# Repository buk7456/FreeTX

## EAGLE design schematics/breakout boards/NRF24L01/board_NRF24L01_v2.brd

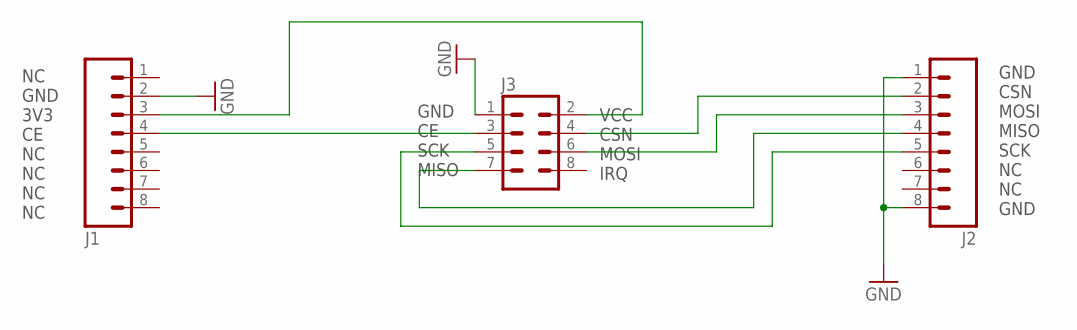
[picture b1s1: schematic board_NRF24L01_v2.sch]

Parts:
J1, J2: M08; 1X08_ROUND
J3: M04X2; 2X4

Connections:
GND: J1.2, J2.1, J2.8, J3.1
unnamed: J1.3, J3.2
unnamed: J2.5, J3.5
unnamed: J2.4, J3.7
unnamed: J2.3, J3.6
unnamed: J1.4, J3.3
unnamed: J2.2, J3.4

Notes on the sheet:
VCC CSN MOSI IRQ
GND CE SCK MISO
GND CSN MOSI MISO SCK NC NC GND
NC GND 3V3 CE NC NC NC NC

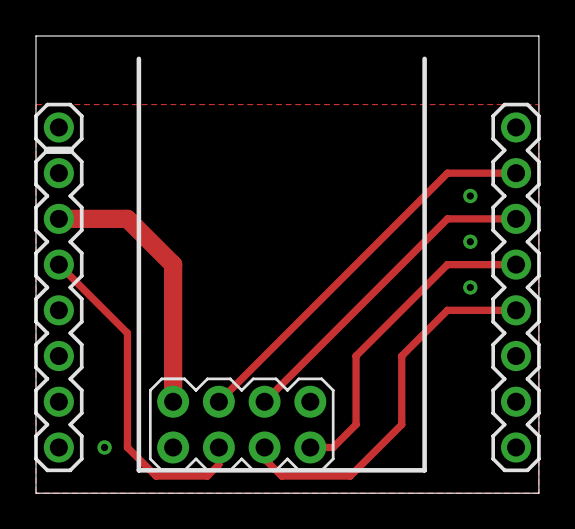
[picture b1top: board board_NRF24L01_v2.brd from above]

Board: 2 copper layers, 27.9 x 25.4 mm, 3 parts (0 on the bottom side), 7 nets.

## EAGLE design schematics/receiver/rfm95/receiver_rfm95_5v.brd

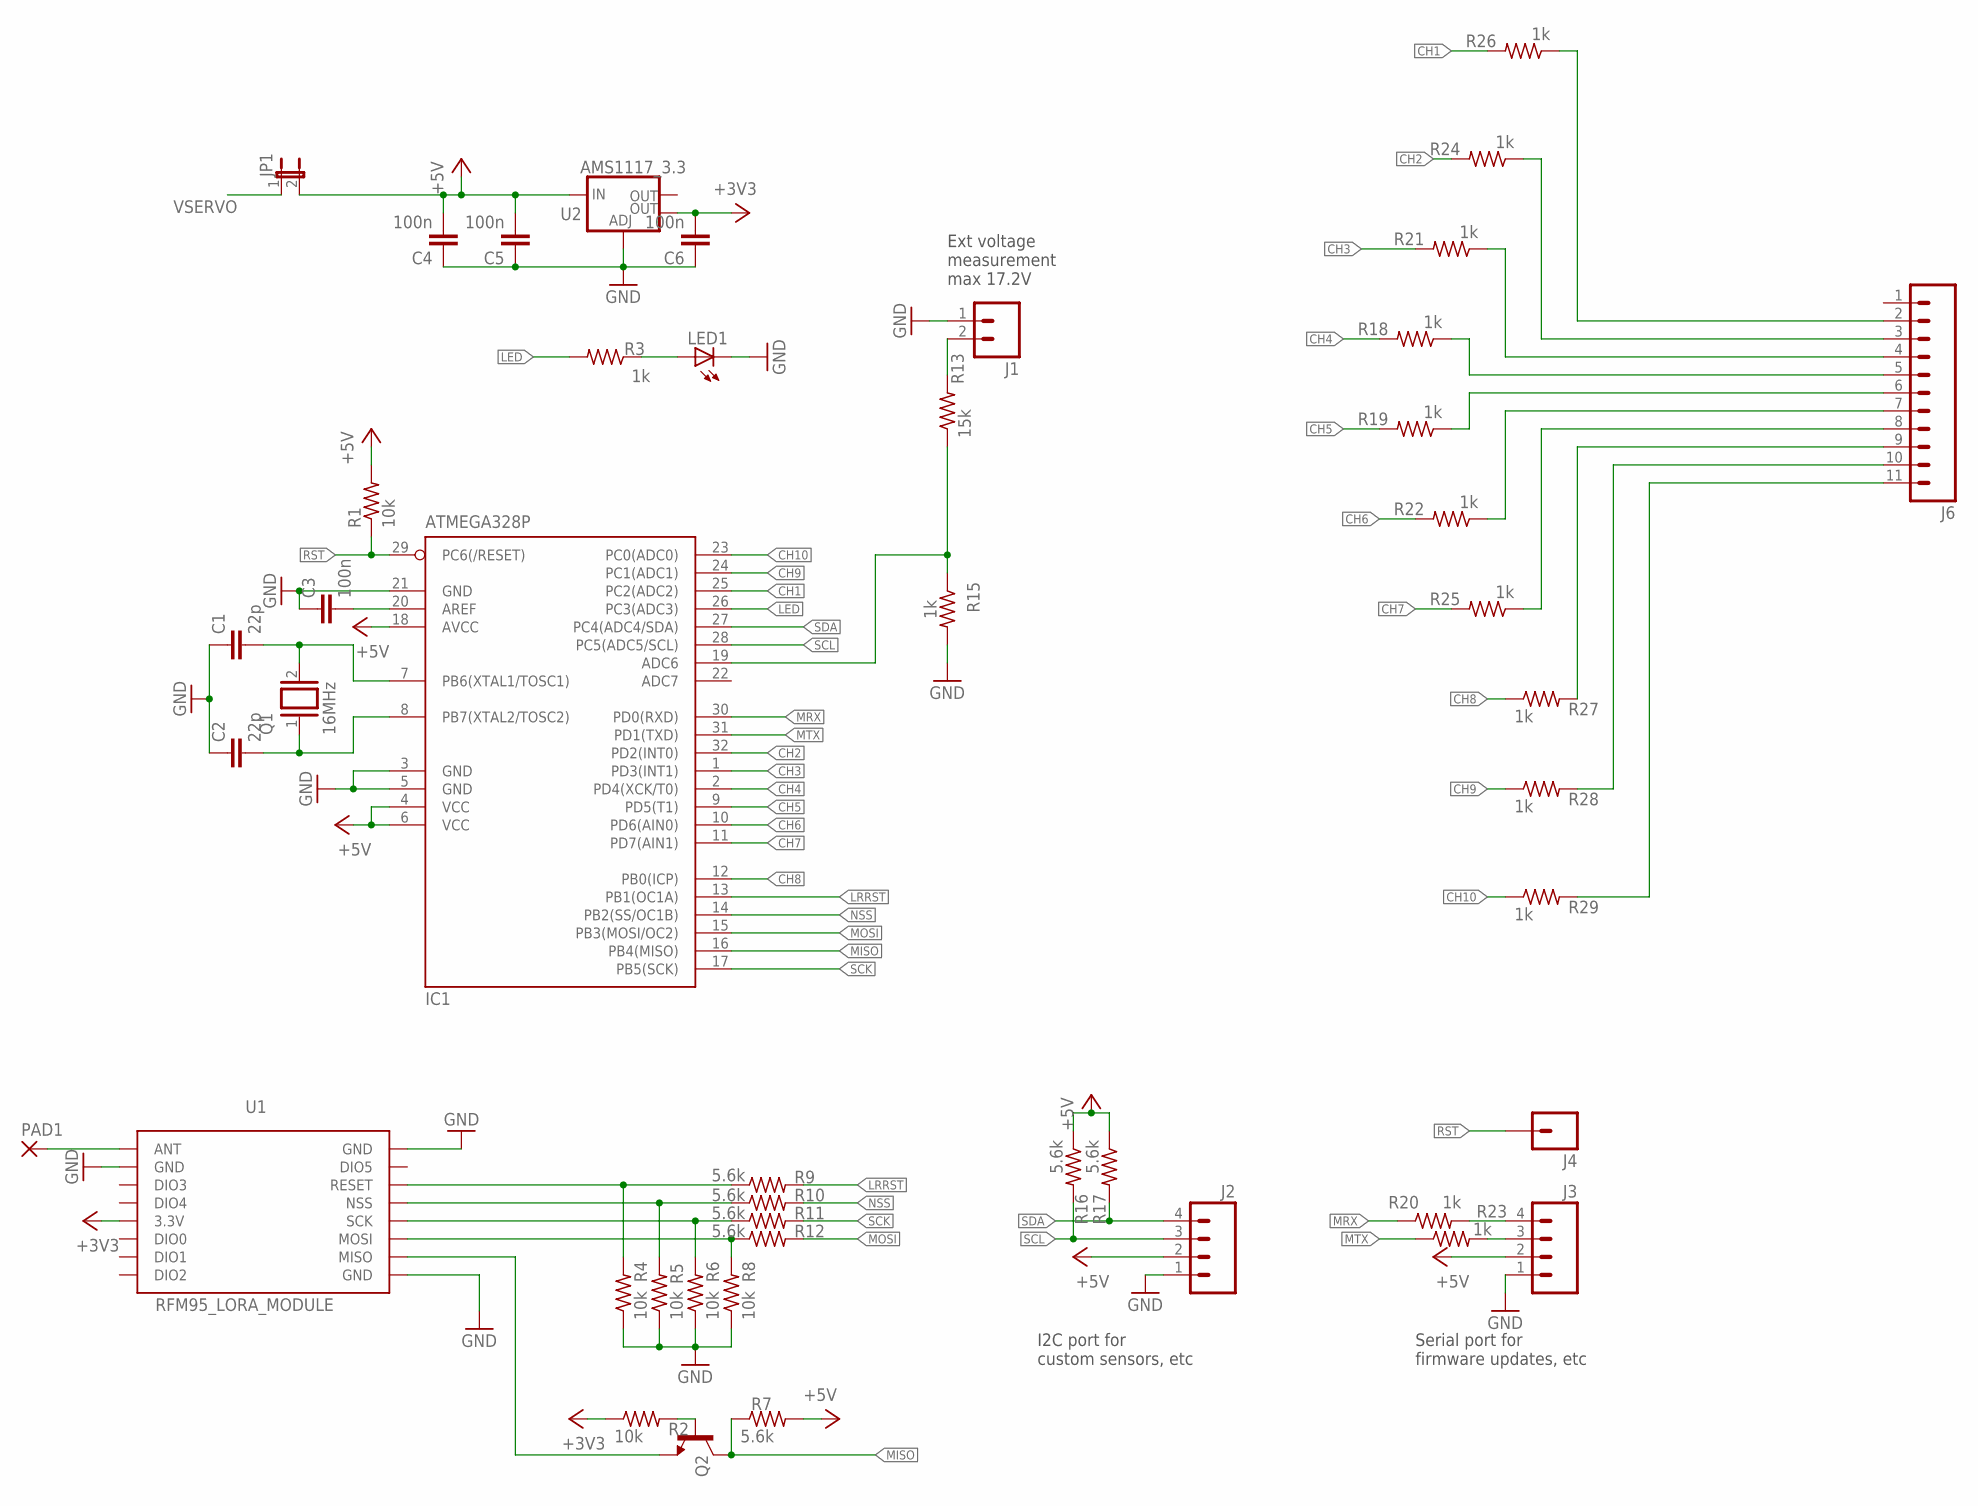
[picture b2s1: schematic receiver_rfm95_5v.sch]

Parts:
C1, C2: 22p; C0805K
C3, C4, C5, C6: 100n; C0805K
IC1: ATMEGA328P; TQFP32-08
J1: M02PTH; 1X02
J2, J3: M04PTH; 1X04
J4: M01PTH; 1X01
J6: M11PTH; 1X11
JP1: JP1E; JP1
LED1: LEDCHIPLED_1206; CHIPLED_1206
PAD1: 2,15/1,0
Q1: 16MHz; QS
Q2: BC817-16SMD; SOT23-BEC
R1, R2, R4, R5, R6, R8: 10k; R0805
R3, R15, R18, R19, R20, R21, R22, R23, R24, R25, R26, R27, R28, R29: 1k; R0805
R7, R9, R10, R11, R12, R16, R17: 5.6k; R0805
R13: 15k; R0805
U1: RFM95_LORA_MODULE; RFM95
U2: AMS1117_3.3; SOT223

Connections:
+3V3: C6.2, R2.1, U1.3.3V, U2.4 (OUT)
+5V: C4.2, C5.2, IC1.4 (VCC), IC1.6 (VCC), IC1.18 (AVCC), J2.2, J3.2, JP1.2, R1.2, R7.2, R16.1, R17.1, U2.3 (IN)
CH1: IC1.25 (PC2(ADC2)), R26.2
CH2: IC1.32 (PD2(INT0)), R24.2
CH3: IC1.1 (PD3(INT1)), R21.2
CH4: IC1.2 (PD4(XCK/T0)), R18.2
CH5: IC1.9 (PD5(T1)), R19.2
CH6: IC1.10 (PD6(AIN0)), R22.2
CH7: IC1.11 (PD7(AIN1)), R25.2
CH8: IC1.12 (PB0(ICP)), R27.1
CH9: IC1.24 (PC1(ADC1)), R28.1
CH10: IC1.23 (PC0(ADC0)), R29.1
DIO3: U1.DIO3
GND: C1.1, C2.1, C3.1, C4.1, C5.1, C6.1, IC1.3 (GND), IC1.5 (GND), IC1.21 (GND), J1.1, J2.1, J3.1, LED1.C, R4.1, R5.1, R6.1, R8.1, R15.2, U1.GND, U1.GND@1 (GND), U1.GND@2 (GND), U2.1 (ADJ)
LED: IC1.26 (PC3(ADC3)), R3.2
LRRST: IC1.13 (PB1(OC1A)), R9.2
MISO: IC1.16 (PB4(MISO)), Q2.C, R7.1
MOSI: IC1.15 (PB3(MOSI/OC2)), R12.2
MRX: IC1.30 (PD0(RXD)), R20.1
MTX: IC1.31 (PD1(TXD)), R23.1
unnamed: C1.2, IC1.7 (PB6(XTAL1/TOSC1)), Q1.2
unnamed: J6.10, R28.2
unnamed: C2.2, IC1.8 (PB7(XTAL2/TOSC2)), Q1.1
unnamed: J6.9, R27.2
unnamed: R4.2, R9.1, U1.RESET
unnamed: R5.2, R10.1, U1.NSS
unnamed: R6.2, R11.1, U1.SCK
unnamed: R8.2, R12.1, U1.MOSI
unnamed: Q2.E, U1.MISO
unnamed: C3.2, IC1.20 (AREF)
unnamed: IC1.19 (ADC6), R13.1, R15.1
unnamed: J3.3, R23.2
unnamed: LED1.A, R3.1
unnamed: PAD1.1, U1.ANT
unnamed: J6.2, R26.1
unnamed: J3.4, R20.2
unnamed: J6.3, R24.1
unnamed: J6.4, R21.1
unnamed: J6.5, R18.1
unnamed: J6.6, R19.1
unnamed: J6.7, R22.1
unnamed: J6.8, R25.1
unnamed: Q2.B, R2.2
unnamed: J1.2, R13.2
unnamed: J6.11, R29.2
NSS: IC1.14 (PB2(SS/OC1B)), R10.2
RST: IC1.29 (PC6(/RESET)), J4.1, R1.1
SCK: IC1.17 (PB5(SCK)), R11.2
SCL: IC1.28 (PC5(ADC5/SCL)), J2.3, R16.2
SDA: IC1.27 (PC4(ADC4/SDA)), J2.4, R17.2
VSERVO: JP1.1

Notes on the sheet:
I2C port for custom sensors, etc
Serial port for firmware updates, etc
Ext voltage measurement max 17.2V

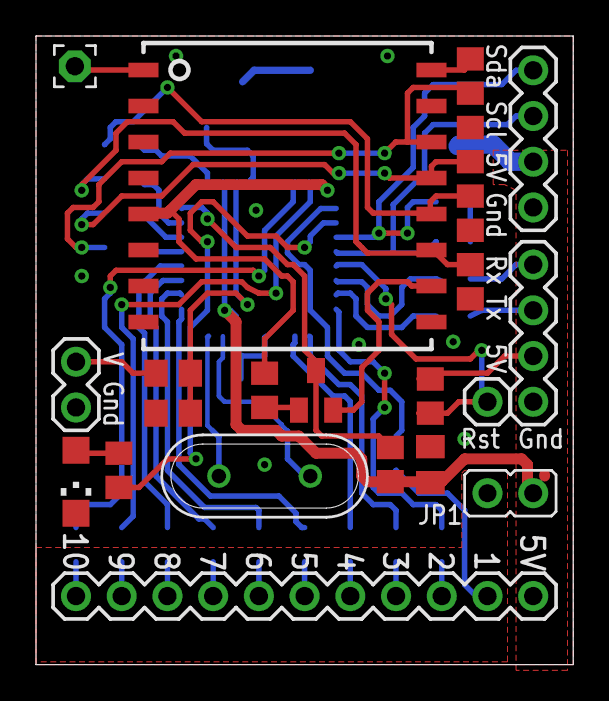
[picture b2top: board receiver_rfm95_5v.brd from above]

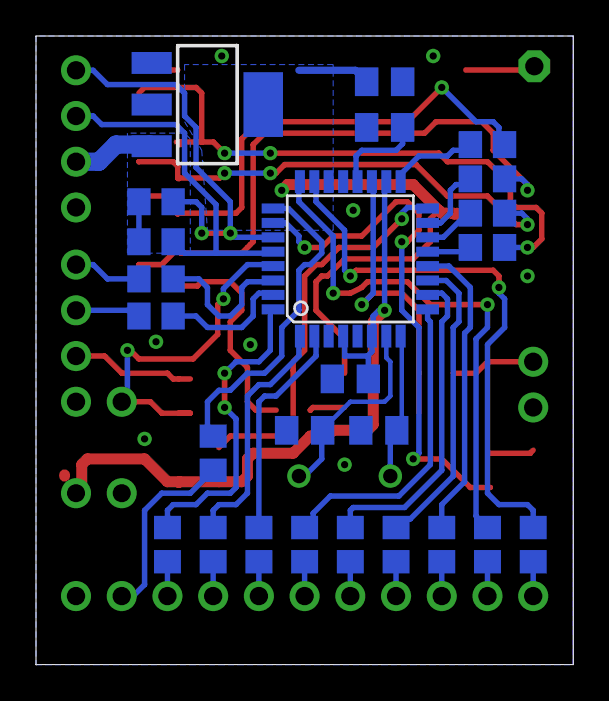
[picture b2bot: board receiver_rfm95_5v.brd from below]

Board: 2 copper layers, 29.8 x 34.9 mm, 47 parts (25 on the bottom side), 49 nets.

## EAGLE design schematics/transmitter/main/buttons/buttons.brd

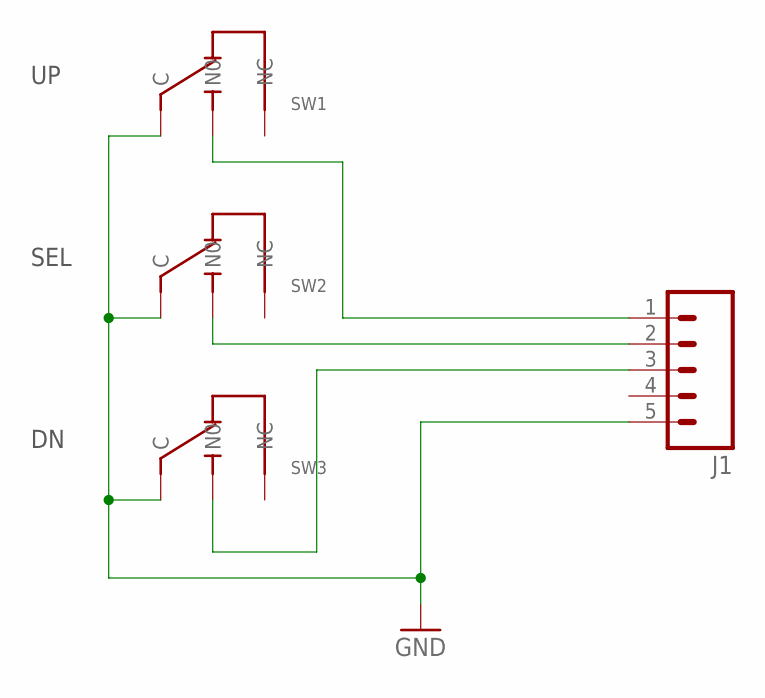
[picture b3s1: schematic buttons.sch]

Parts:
J1: M05PTH; 1X05
SW1, SW2, SW3: MICROSWITCH

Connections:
GND: J1.5, SW1.C, SW2.C, SW3.C
unnamed: J1.1, SW1.NO (N0)
unnamed: J1.3, SW3.NO (N0)
unnamed: J1.2, SW2.NO (N0)

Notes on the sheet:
SEL

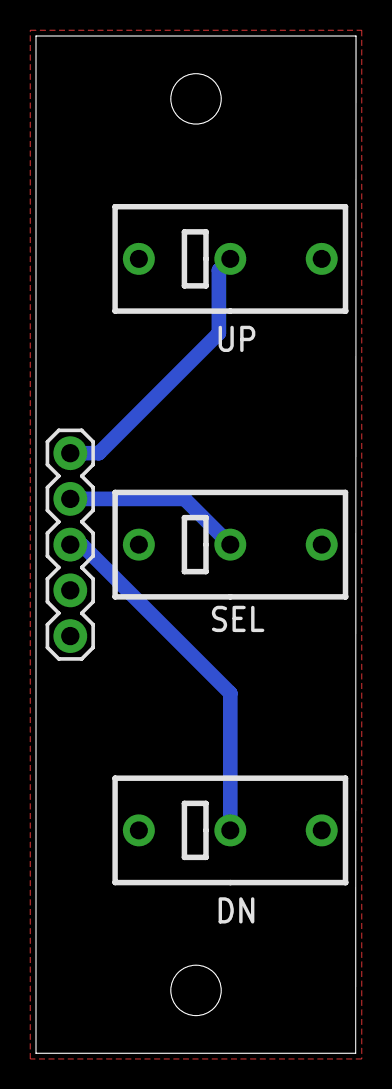
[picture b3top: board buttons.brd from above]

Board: 2 copper layers, 17.8 x 56.5 mm, 4 parts (0 on the bottom side), 4 nets.

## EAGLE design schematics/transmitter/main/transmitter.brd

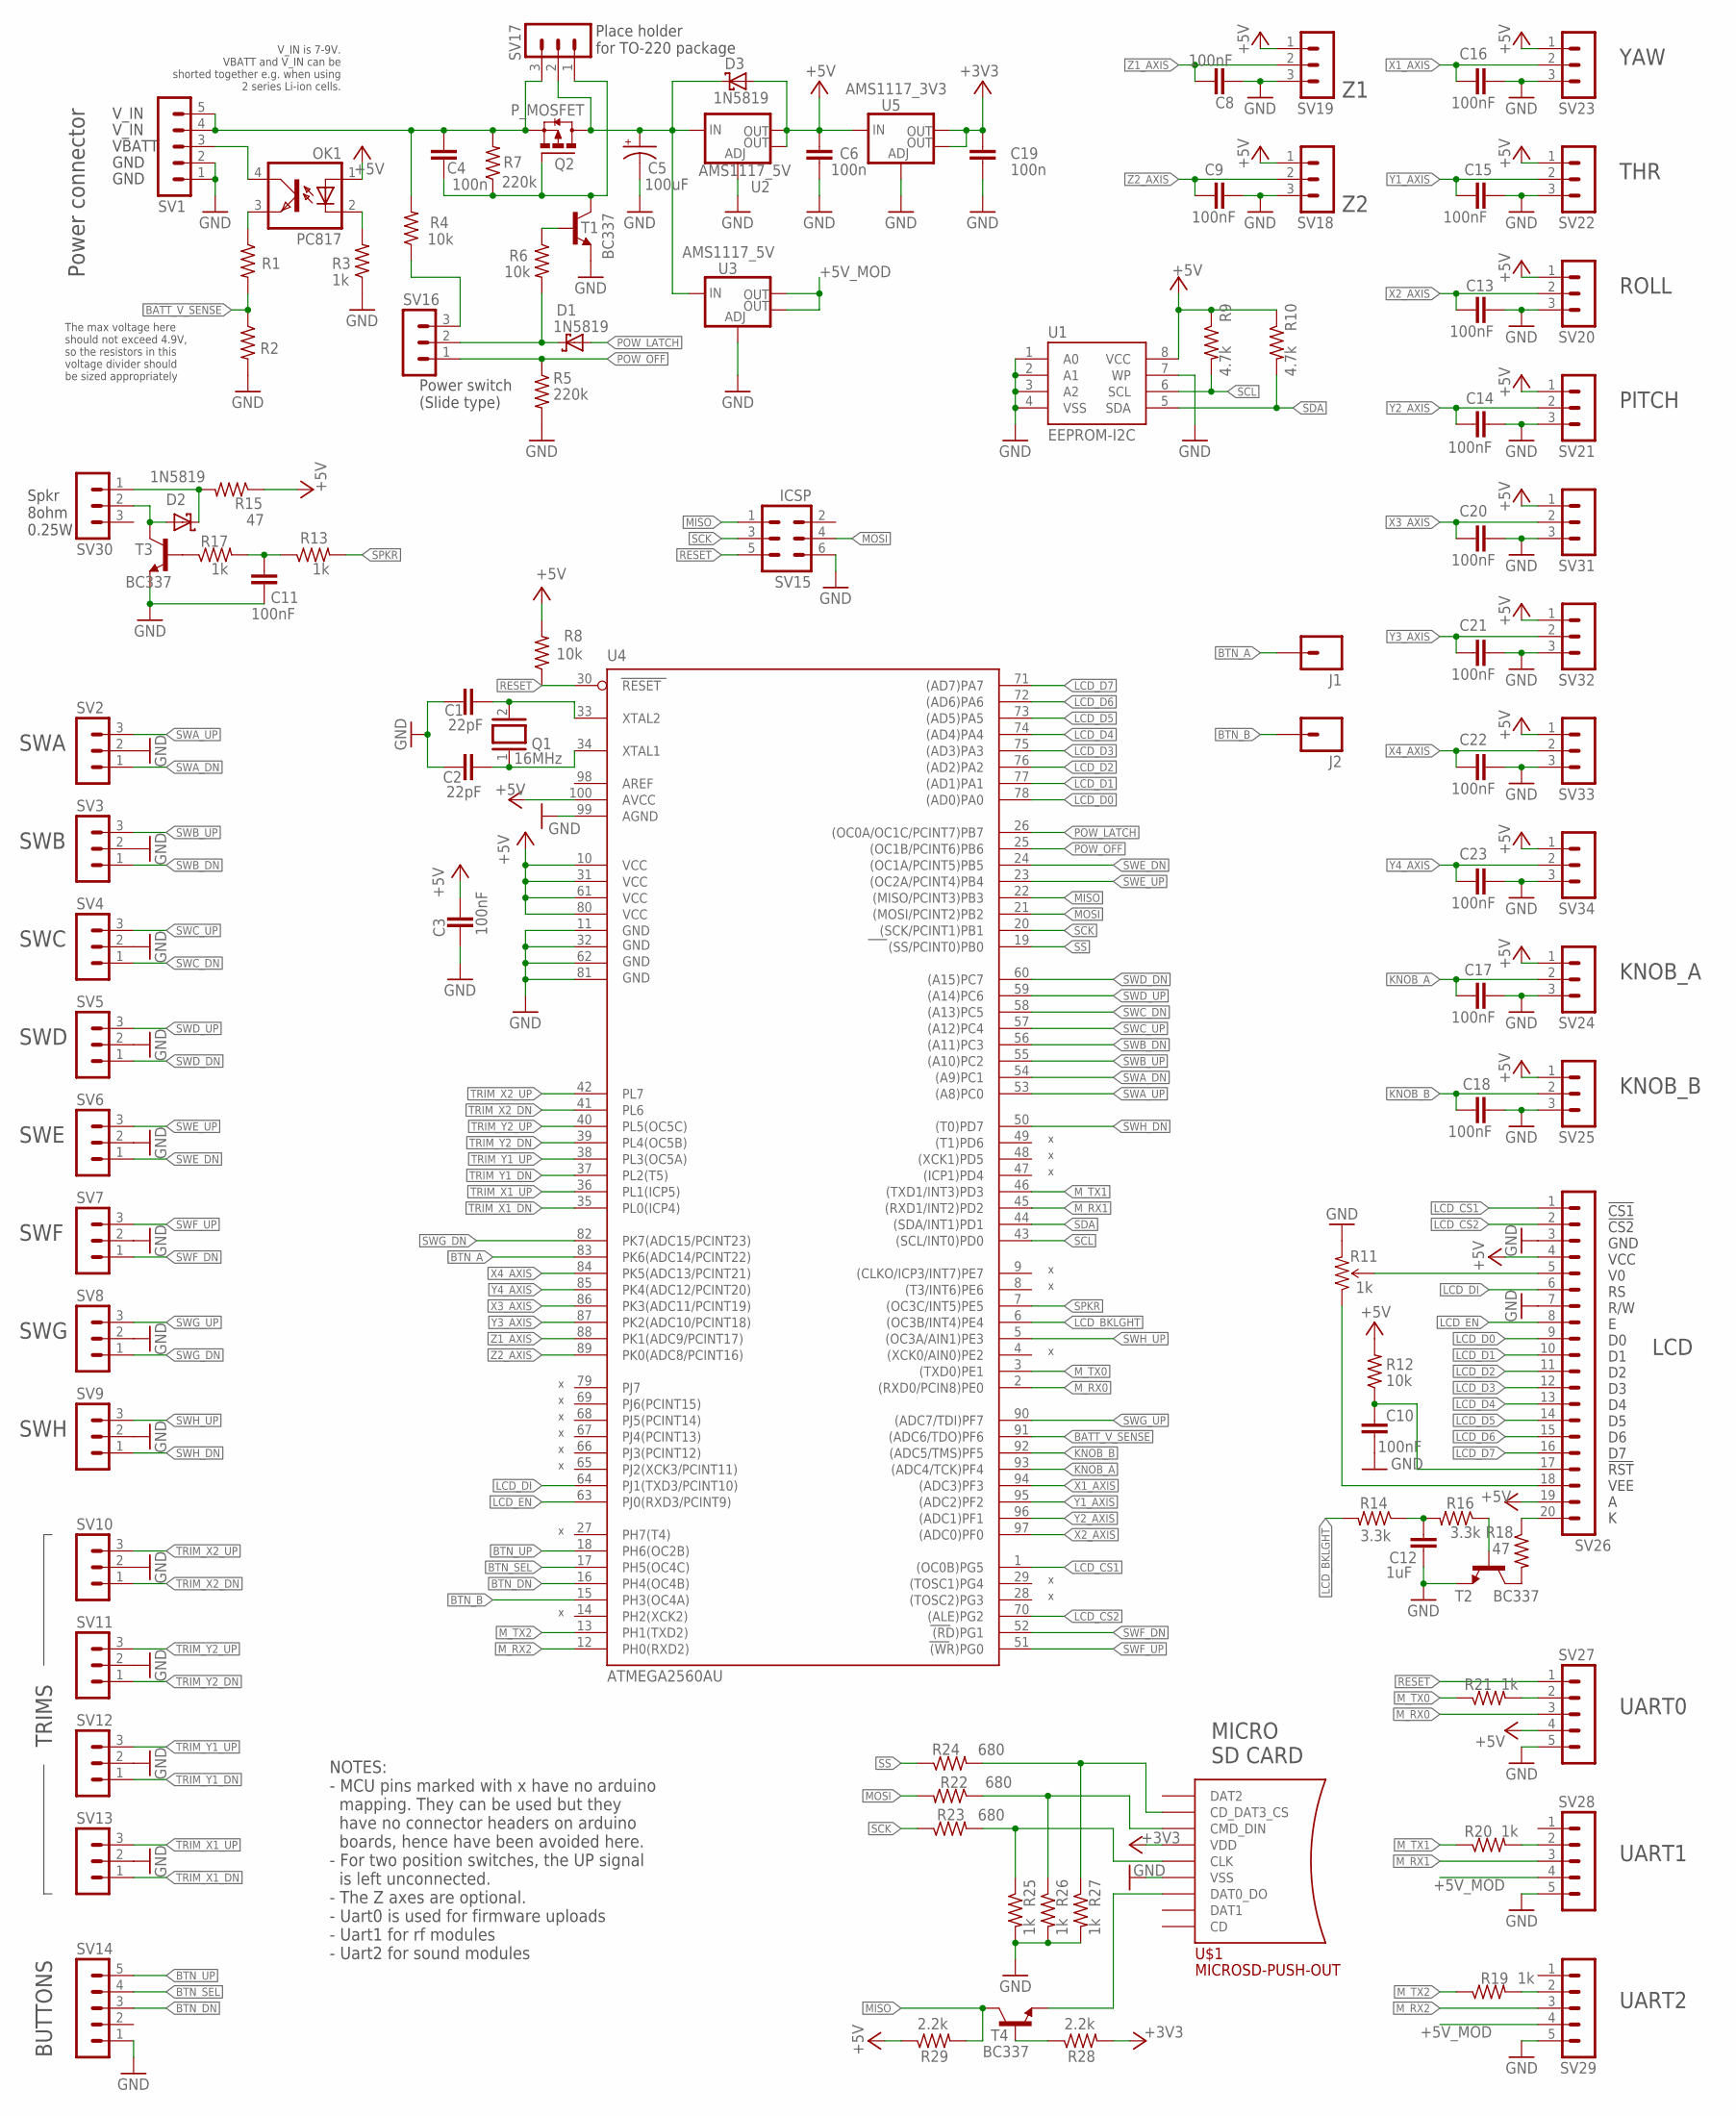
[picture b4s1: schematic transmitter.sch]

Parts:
C1, C2: 22pF; C050-024X044
C3, C8, C9, C10, C11, C13, C14, C15, C16, C17, C18, C20, C21, C22, C23: 100nF; C050-024X044
C4, C6, C19: 100n; C050-024X044
C5: 100uF; E2,5-6E
C12: 1uF; C050-024X044
D1, D2, D3: 1N5819; DO41-7.6
J1, J2: M01PTH_LONGPAD; 1X01_LONGPAD
OK1: PC817; DIL04
Q1: 16MHz; QS
Q2: P_MOSFET; SUPER-SOT3
R1, R2, R3, R13, R17, R19, R20, R21, R25, R26, R27: 1k; 0204/5
R4, R6, R8, R12: 10k; 0204/5
R5, R7: 220k; 0204/5
R9, R10: 4.7k; 0204/5
R11: 1k; TRIM_POT_PTH
R14, R16: 3.3k; 0204/5
R15, R18: 47; 0204/5
R22, R23, R24: 680; 0204/5
R28, R29: 2.2k; 0204/5
SV1, SV14, SV27, SV28, SV29: MA05-1
SV2, SV3, SV4, SV5, SV6, SV7, SV8, SV9, SV10, SV11, SV12, SV13, SV16, SV17, SV18, SV19, SV20, SV21, SV22, SV23, SV24, SV25, SV30, SV31, SV32, SV33, SV34: MA03-1
SV15: ICSP; MA03-2
SV26: MA20-1
T1, T2, T3, T4: BC337; TO92
U1: EEPROM-I2C; SO08-EIAJ
U2, U3: AMS1117_5V; SOT223
U4: ATMEGA2560AU; TQFP100
U5: AMS1117_3V3; SOT223
U$1: MICROSD-PUSH-OUT

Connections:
+3V3: C19.2, R28.2, U5.2 (OUT), U5.4 (OUT), U$1.4 (VDD)
+5V: C3.1, C6.2, D3.A, OK1.1 (A), R8.2, R9.1, R10.1, R12.2, R15.1, R29.1, SV18.1, SV19.1, SV20.1, SV21.1, SV22.1, SV23.1, SV24.1, SV25.1, SV26.4, SV26.19, SV27.4, SV31.1, SV32.1, SV33.1, SV34.1, U1.8 (VCC), U2.2 (OUT), U2.4 (OUT), U4.10 (VCC), U4.31 (VCC1), U4.61 (VCC2), U4.80 (VCC3), U4.100 (AVCC), U5.3 (IN)
+5V_MOD: SV28.4, SV29.4, U3.2 (OUT), U3.4 (OUT)
BATT_V_SENSE: R1.2, R2.1, U4.91 ((ADC6/TDO)PF6)
BTN_A: J1.1, U4.83 (PK6(ADC14/PCINT22))
BTN_B: J2.1, U4.15 (PH3(OC4A))
BTN_DN: SV14.3, U4.16 (PH4(OC4B))
BTN_SEL: SV14.4, U4.17 (PH5(OC4C))
BTN_UP: SV14.5, U4.18 (PH6(OC2B))
GND: C1.1, C2.1, C3.2, C5.-, C6.1, C8.2, C9.1, C10.2, C11.2, C12.2, C13.1, C14.1, C15.1, C16.1, C17.1, C18.1, C19.1, C20.1, C21.1, C22.1, C23.1, R2.2, R3.1, R5.2, R11.3 (CW), R25.2, R26.2, R27.2, SV1.1, SV1.2, SV2.2, SV3.2, SV4.2, SV5.2, SV6.2, SV7.2, SV8.2, SV9.2, SV10.2, SV11.2, SV12.2, SV13.2, SV14.1, SV15.6, SV18.3, SV19.3, SV20.3, SV21.3, SV22.3, SV23.3, SV24.3, SV25.3, SV26.3, SV26.7, SV27.5, SV28.5, SV29.5, SV31.3, SV32.3, SV33.3, SV34.3, T1.1 (E), T2.1 (E), T3.1 (E), U1.1 (A0), U1.2 (A1), U1.3 (A2), U1.4 (VSS), U1.7 (WP), U2.1 (ADJ), U3.1 (ADJ), U4.11 (GND), U4.32 (GND1), U4.62 (GND2), U4.81 (GND3), U4.99 (AGND), U5.1 (ADJ), U$1.6 (VSS), U$1.G1 (VSS), U$1.G2 (VSS), U$1.G3 (VSS), U$1.G4 (VSS)
KNOB_A: C17.2, SV24.2, U4.93 ((ADC4/TCK)PF4)
KNOB_B: C18.2, SV25.2, U4.92 ((ADC5/TMS)PF5)
LCD_BKLGHT: R14.2, U4.6 ((OC3B/INT4)PE4)
LCD_CS1: SV26.1, U4.1 ((OC0B)PG5)
LCD_CS2: SV26.2, U4.70 ((ALE)PG2)
LCD_D0: SV26.9, U4.78 ((AD0)PA0)
LCD_D1: SV26.10, U4.77 ((AD1)PA1)
LCD_D2: SV26.11, U4.76 ((AD2)PA2)
LCD_D3: SV26.12, U4.75 ((AD3)PA3)
LCD_D4: SV26.13, U4.74 ((AD4)PA4)
LCD_D5: SV26.14, U4.73 ((AD5)PA5)
LCD_D6: SV26.15, U4.72 ((AD6)PA6)
LCD_D7: SV26.16, U4.71 ((AD7)PA7)
LCD_DI: SV26.6, U4.64 (PJ1(TXD3/PCINT10))
LCD_EN: SV26.8, U4.63 (PJ0(RXD3/PCINT9))
MISO: R29.2, SV15.1, T4.3 (C), U4.22 ((MISO/PCINT3)PB3)
MOSI: R22.2, SV15.4, U4.21 ((MOSI/PCINT2)PB2)
M_RX0: SV27.3, U4.2 ((RXD0/PCIN8)PE0)
M_RX1: SV28.3, U4.45 ((RXD1/INT2)PD2)
M_RX2: SV29.3, U4.12 (PH0(RXD2))
M_TX0: R21.1, U4.3 ((TXD0)PE1)
M_TX1: R20.1, U4.46 ((TXD1/INT3)PD3)
M_TX2: R19.1, U4.13 (PH1(TXD2))
unnamed: C12.1, R14.1, R16.2
unnamed: C10.1, R12.1, SV26.17
unnamed: R18.2, T2.3 (C)
unnamed: R16.1, T2.2 (B)
unnamed: C11.1, R13.1, R17.2
unnamed: R21.2, SV27.2
unnamed: R20.2, SV28.2
unnamed: R19.2, SV29.2
unnamed: C1.2, Q1.2, U4.33 (XTAL2)
unnamed: C2.2, Q1.1, U4.34 (XTAL1)
unnamed: T4.1 (E), U$1.7 (DAT0_DO)
unnamed: OK1.4 (COL), SV1.3
unnamed: R11.1 (CCW), SV26.18
unnamed: R11.2 (WIPER), SV26.5
unnamed: R18.1, SV26.20
unnamed: R24.2, R27.1, U$1.2 (CD_DAT3_CS)
unnamed: R22.1, R26.1, U$1.3 (CMD_DIN)
unnamed: R23.2, R25.1, U$1.5 (CLK)
unnamed: R28.1, T4.2 (B)
unnamed: R17.1, T3.2 (B)
unnamed: D2.A, SV30.2, T3.3 (C)
unnamed: D2.C, R15.2, SV30.1
unnamed: R6.1, T1.2 (B)
unnamed: D1.C, R6.2, SV16.2
unnamed: OK1.3 (EMIT), R1.1
unnamed: C4.2, Q2.2 (S), R4.2, R7.2, SV1.4, SV1.5, SV17.3
unnamed: C4.1, Q2.1 (G), R7.1, SV17.1, T1.3 (C)
unnamed: OK1.2 (C), R3.2
unnamed: R4.1, SV16.3
unnamed: C5.+, D3.C, Q2.3 (D), SV17.2, U2.3 (IN), U3.3 (IN)
POW_LATCH: D1.A, U4.26 ((OC0A/OC1C/PCINT7)PB7)
POW_OFF: R5.1, SV16.1, U4.25 ((OC1B/PCINT6)PB6)
RESET: R8.1, SV15.5, SV27.1, U4.30 (RESET)
SCK: R23.1, SV15.3, U4.20 ((SCK/PCINT1)PB1)
SCL: R9.2, U1.6 (SCL), U4.43 ((SCL/INT0)PD0)
SDA: R10.2, U1.5 (SDA), U4.44 ((SDA/INT1)PD1)
SPKR: R13.2, U4.7 ((OC3C/INT5)PE5)
SS: R24.1, U4.19 ((SS/PCINT0)PB0)
SWA_DN: SV2.1, U4.54 ((A9)PC1)
SWA_UP: SV2.3, U4.53 ((A8)PC0)
SWB_DN: SV3.1, U4.56 ((A11)PC3)
SWB_UP: SV3.3, U4.55 ((A10)PC2)
SWC_DN: SV4.1, U4.58 ((A13)PC5)
SWC_UP: SV4.3, U4.57 ((A12)PC4)
SWD_DN: SV5.1, U4.60 ((A15)PC7)
SWD_UP: SV5.3, U4.59 ((A14)PC6)
SWE_DN: SV6.1, U4.24 ((OC1A/PCINT5)PB5)
SWE_UP: SV6.3, U4.23 ((OC2A/PCINT4)PB4)
SWF_DN: SV7.1, U4.52 ((RD)PG1)
SWF_UP: SV7.3, U4.51 ((WR)PG0)
SWG_DN: SV8.1, U4.82 (PK7(ADC15/PCINT23))
SWG_UP: SV8.3, U4.90 ((ADC7/TDI)PF7)
SWH_DN: SV9.1, U4.50 ((T0)PD7)
SWH_UP: SV9.3, U4.5 ((OC3A/AIN1)PE3)
TRIM_X1_DN: SV13.1, U4.35 (PL0(ICP4))
TRIM_X1_UP: SV13.3, U4.36 (PL1(ICP5))
TRIM_X2_DN: SV10.1, U4.41 (PL6)
TRIM_X2_UP: SV10.3, U4.42 (PL7)
TRIM_Y1_DN: SV12.1, U4.37 (PL2(T5))
TRIM_Y1_UP: SV12.3, U4.38 (PL3(OC5A))
TRIM_Y2_DN: SV11.1, U4.39 (PL4(OC5B))
TRIM_Y2_UP: SV11.3, U4.40 (PL5(OC5C))
X1_AXIS: C16.2, SV23.2, U4.94 ((ADC3)PF3)
X2_AXIS: C13.2, SV20.2, U4.97 ((ADC0)PF0)
X3_AXIS: C20.2, SV31.2, U4.86 (PK3(ADC11/PCINT19))
X4_AXIS: C22.2, SV33.2, U4.84 (PK5(ADC13/PCINT21))
Y1_AXIS: C15.2, SV22.2, U4.95 ((ADC2)PF2)
Y2_AXIS: C14.2, SV21.2, U4.96 ((ADC1)PF1)
Y3_AXIS: C21.2, SV32.2, U4.87 (PK2(ADC10/PCINT18))
Y4_AXIS: C23.2, SV34.2, U4.85 (PK4(ADC12/PCINT20))
Z1_AXIS: C8.1, SV19.2, U4.88 (PK1(ADC9/PCINT17))
Z2_AXIS: C9.2, SV18.2, U4.89 (PK0(ADC8/PCINT16))

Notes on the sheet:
Spkr 8ohm 0.25W
!CS1 !CS2 GND VCC V0 RS R/W E D0 D1 D2 D3 D4 D5 D6 D7 !RST VEE A K
GND
VBATT
Power connector
The max voltage here should not exceed 4.9V, so the resistors in this voltage divider should be sized appropriately
Power switch (Slide type)
V_IN
V_IN is 7-9V. VBATT and V_IN can be shorted together e.g. when using 2 series Li-ion cells.
SWA
SWB
SWC
SWD
SWE
SWF
SWG
SWH
LCD
UART0
UART1
BUTTONS
TRIMS
ROLL
PITCH
THR
YAW
KNOB_A
KNOB_B
NOTES: - MCU pins marked with x have no arduino mapping. They can be used but they have no connector headers on arduino boards, hence have been avoided here. - For two position switches, the UP signal is left unconnected. - The Z axes are optional. - Uart0 is used for firmware uploads - Uart1 for r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
Place holder for TO-220 package
UART2
MICRO SD CARD

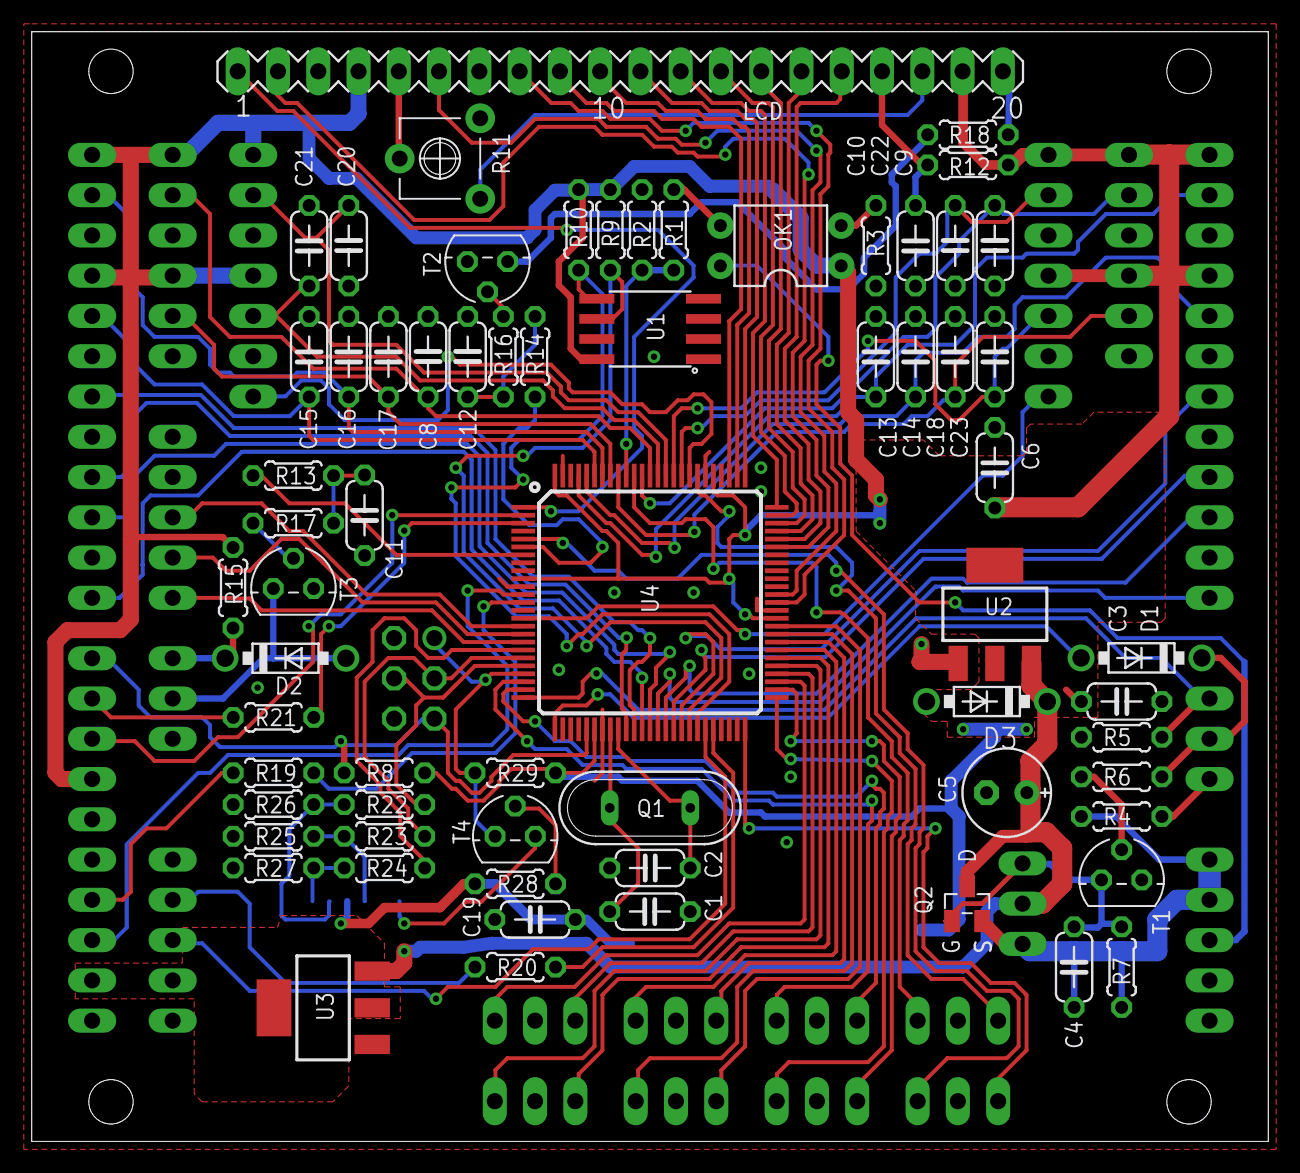
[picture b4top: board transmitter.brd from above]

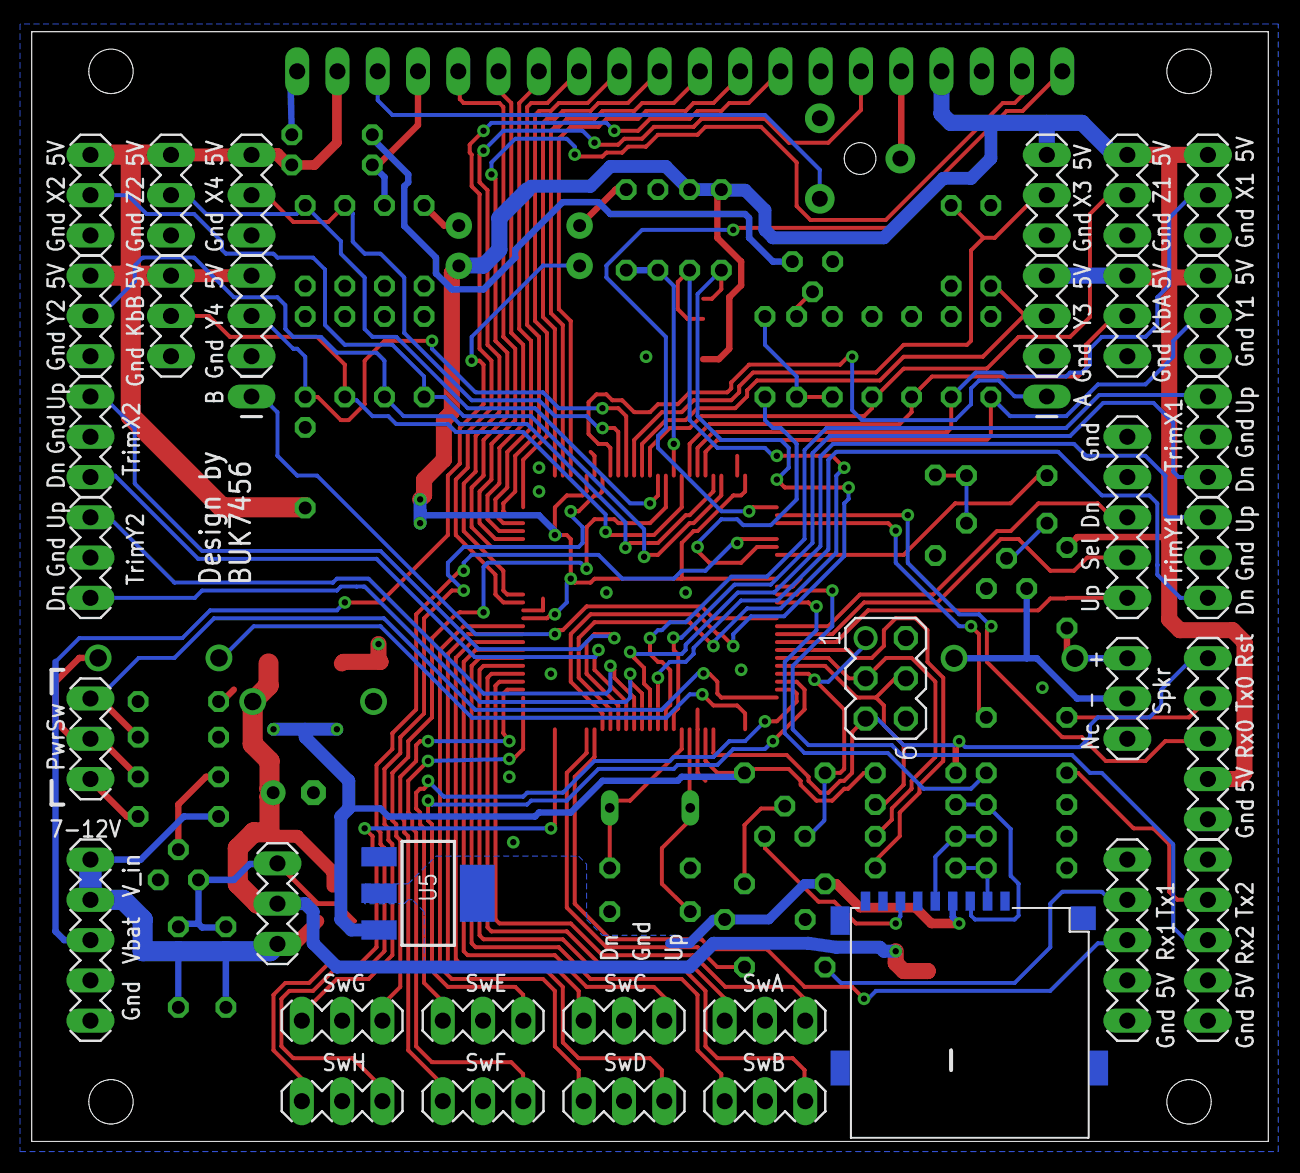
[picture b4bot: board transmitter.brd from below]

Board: 2 copper layers, 78.0 x 70.0 mm, 103 parts (37 on the bottom side), 105 nets.

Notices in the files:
parts and their libraries:
SparkFun-Connectors: Licensing: Creative Commons ShareAlike 4.0 International - https://creativecommons.org/licenses/by-sa/4.0
